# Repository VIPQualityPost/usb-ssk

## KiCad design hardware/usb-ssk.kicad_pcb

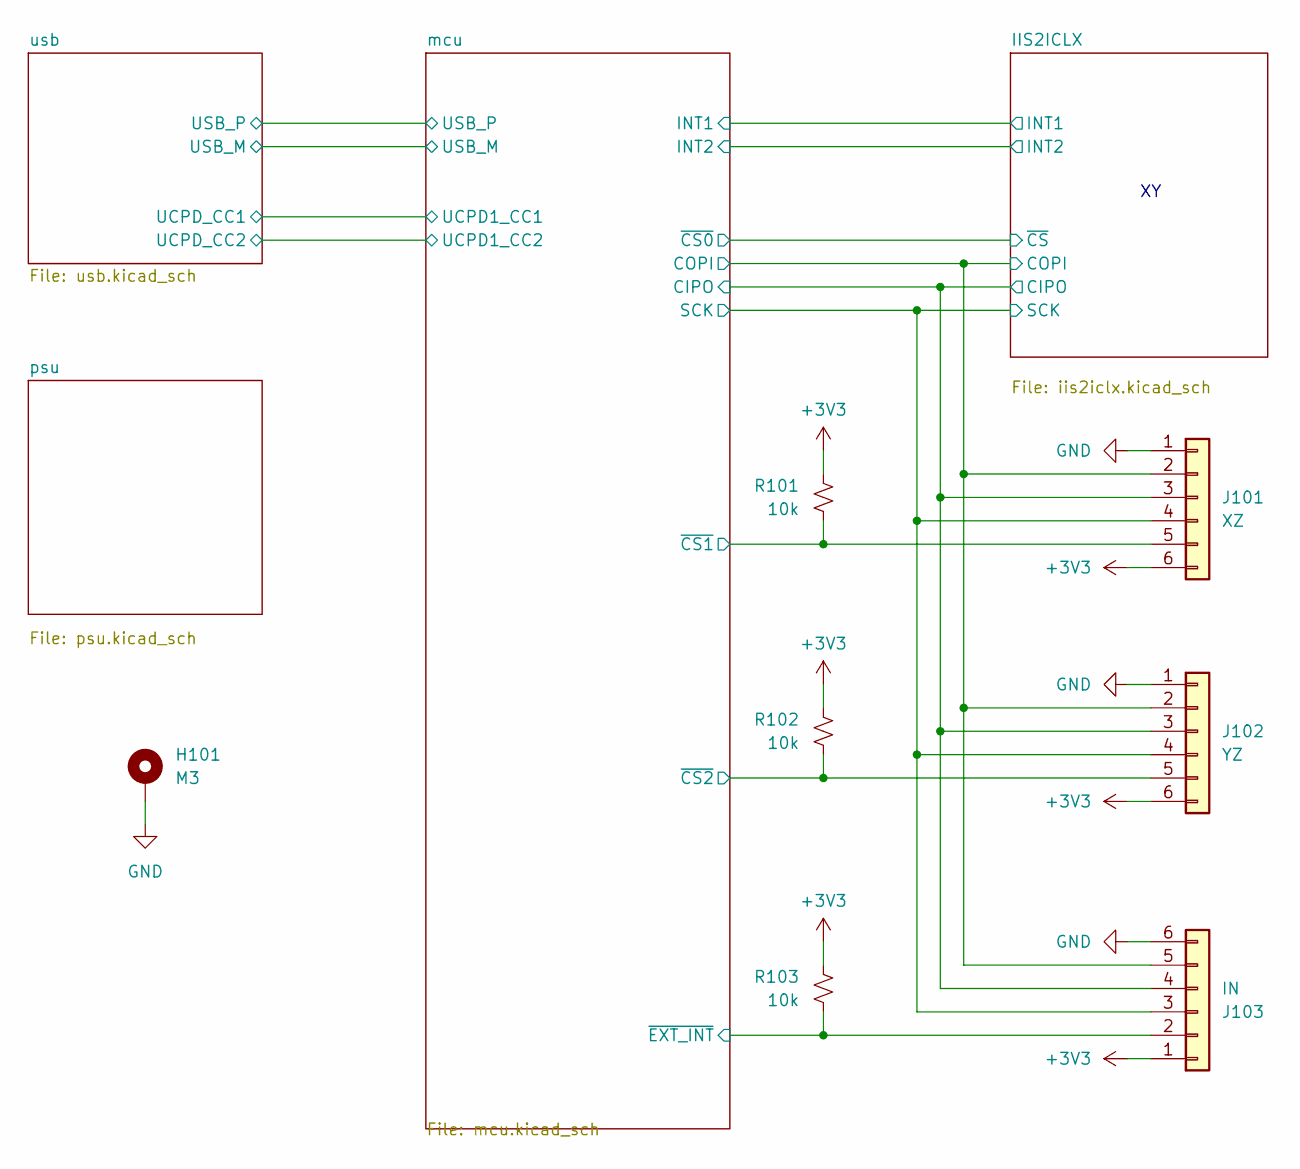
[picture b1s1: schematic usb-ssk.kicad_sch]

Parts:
H101: M3; MountingHole_3.2mm_M3_DIN965_Pad
J101: XZ; FPC-SMD_6P-P0.50_XUNPU_FPC-05F-6PH20; LCSC ID C2856796
J102: YZ; FPC-SMD_6P-P0.50_XUNPU_FPC-05F-6PH20; LCSC ID C2856796
J103: IN; FPC-SMD_6P-P0.50_XUNPU_FPC-05F-6PH20; LCSC ID C2856796
R101, R102, R103: 10k; R_0402_1005Metric; LCSC ID C25744

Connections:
+3V3: J101.6, J102.6, J103.1, R101.1, R102.1, R103.1; also elsewhere on the board
/IIS2ICLX/CIPO: J101.3, J102.3, J103.4; also elsewhere on the board
/IIS2ICLX/COPI: J101.2, J102.2, J103.5; also elsewhere on the board
/IIS2ICLX/SCK: J101.4, J102.4, J103.3; also elsewhere on the board
/mcu/~CS1: J101.5, R101.2; also elsewhere on the board
/mcu/~CS2: J102.5, R102.2; also elsewhere on the board
/mcu/~EXT_INT: J103.2, R103.2; also elsewhere on the board
GND: H101.1, J101.1, J102.1, J103.6; also elsewhere on the board

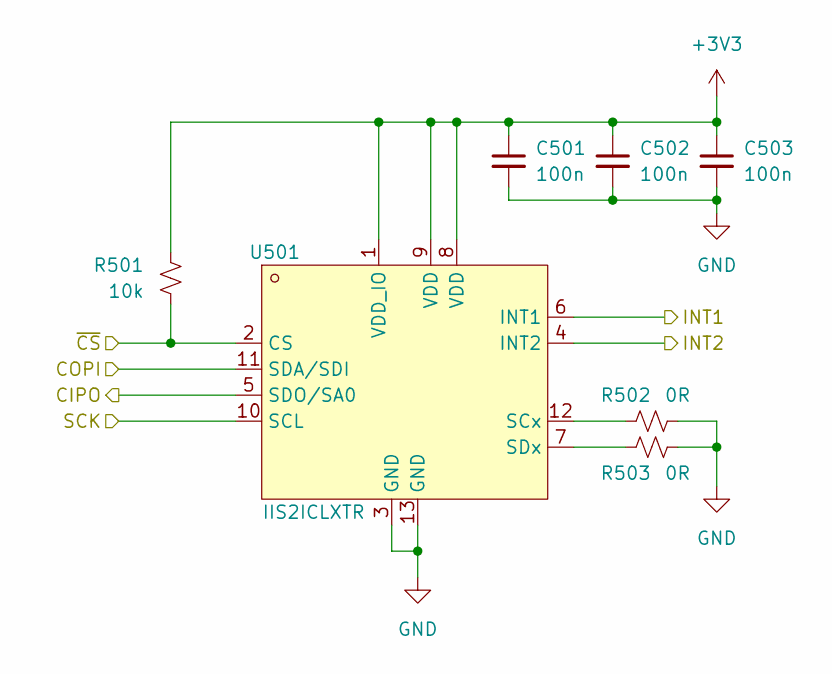
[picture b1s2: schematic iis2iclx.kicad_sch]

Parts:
C501, C502, C503: 100n; C_0402_1005Metric; LCSC ID C1525
R501: 10k; R_0402_1005Metric; LCSC ID C25744
R502, R503: 0R; R_0402_1005Metric; LCSC ID C17168
U501: IIS2ICLXTR; LGA16-L; LCSC ID C1857737

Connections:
+3V3: C501.1, C502.1, C503.1, R501.1, U501.1 (VDD_IO), U501.8 (VDD), U501.9 (VDD); also elsewhere on the board
/IIS2ICLX/CIPO: U501.5 (SDO/SA0); also elsewhere on the board
/IIS2ICLX/COPI: U501.11 (SDA/SDI); also elsewhere on the board
/IIS2ICLX/INT1: U501.6 (INT1); also elsewhere on the board
/IIS2ICLX/INT2: U501.4 (INT2); also elsewhere on the board
/IIS2ICLX/SCK: U501.10 (SCL); also elsewhere on the board
/IIS2ICLX/~CS: R501.2, U501.2 (CS); also elsewhere on the board
GND: C501.2, C502.2, C503.2, R502.2, R503.2, U501.3 (GND), U501.13 (GND); also elsewhere on the board
unnamed: R502.1, U501.12 (SCx)
unnamed: R503.1, U501.7 (SDx)

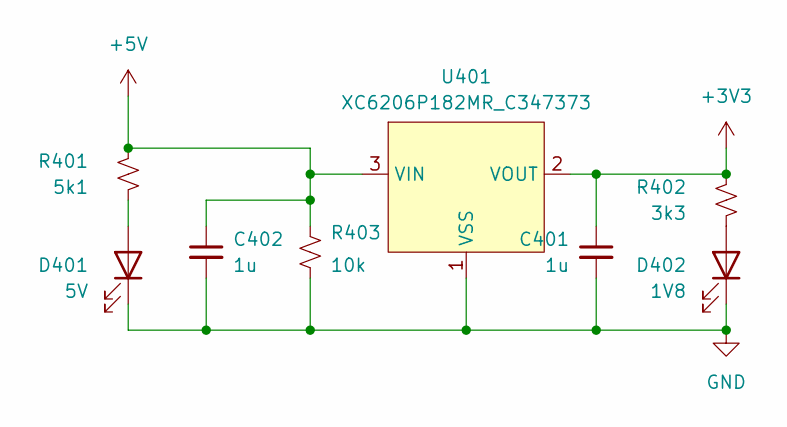
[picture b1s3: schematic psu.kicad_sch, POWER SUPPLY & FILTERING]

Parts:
C401, C402: 1u; C_0402_1005Metric; LCSC ID C52923
D401: 5V; D_0603_1608Metric; LCSC ID C2290
D402: 1V8; D_0603_1608Metric; LCSC ID C2290
R401: 5k1; R_0402_1005Metric; LCSC ID C25905
R402: 3k3; R_0402_1005Metric; LCSC ID C25890
R403: 10k; R_0402_1005Metric; LCSC ID C25744
U401: XC6206P182MR_C347373; SOT-23-3_L3.0-W1.7-P0.95-LS2.9-BR; LCSC Part C347373

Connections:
+3V3: C401.1, R402.1, U401.2 (VOUT); also elsewhere on the board
+5V: C402.1, R401.1, R403.1, U401.3 (VIN); also elsewhere on the board
GND: C401.2, C402.2, D401.1 (K), D402.1 (K), R403.2, U401.1 (VSS); also elsewhere on the board
unnamed: D401.2 (A), R401.2
unnamed: D402.2 (A), R402.2

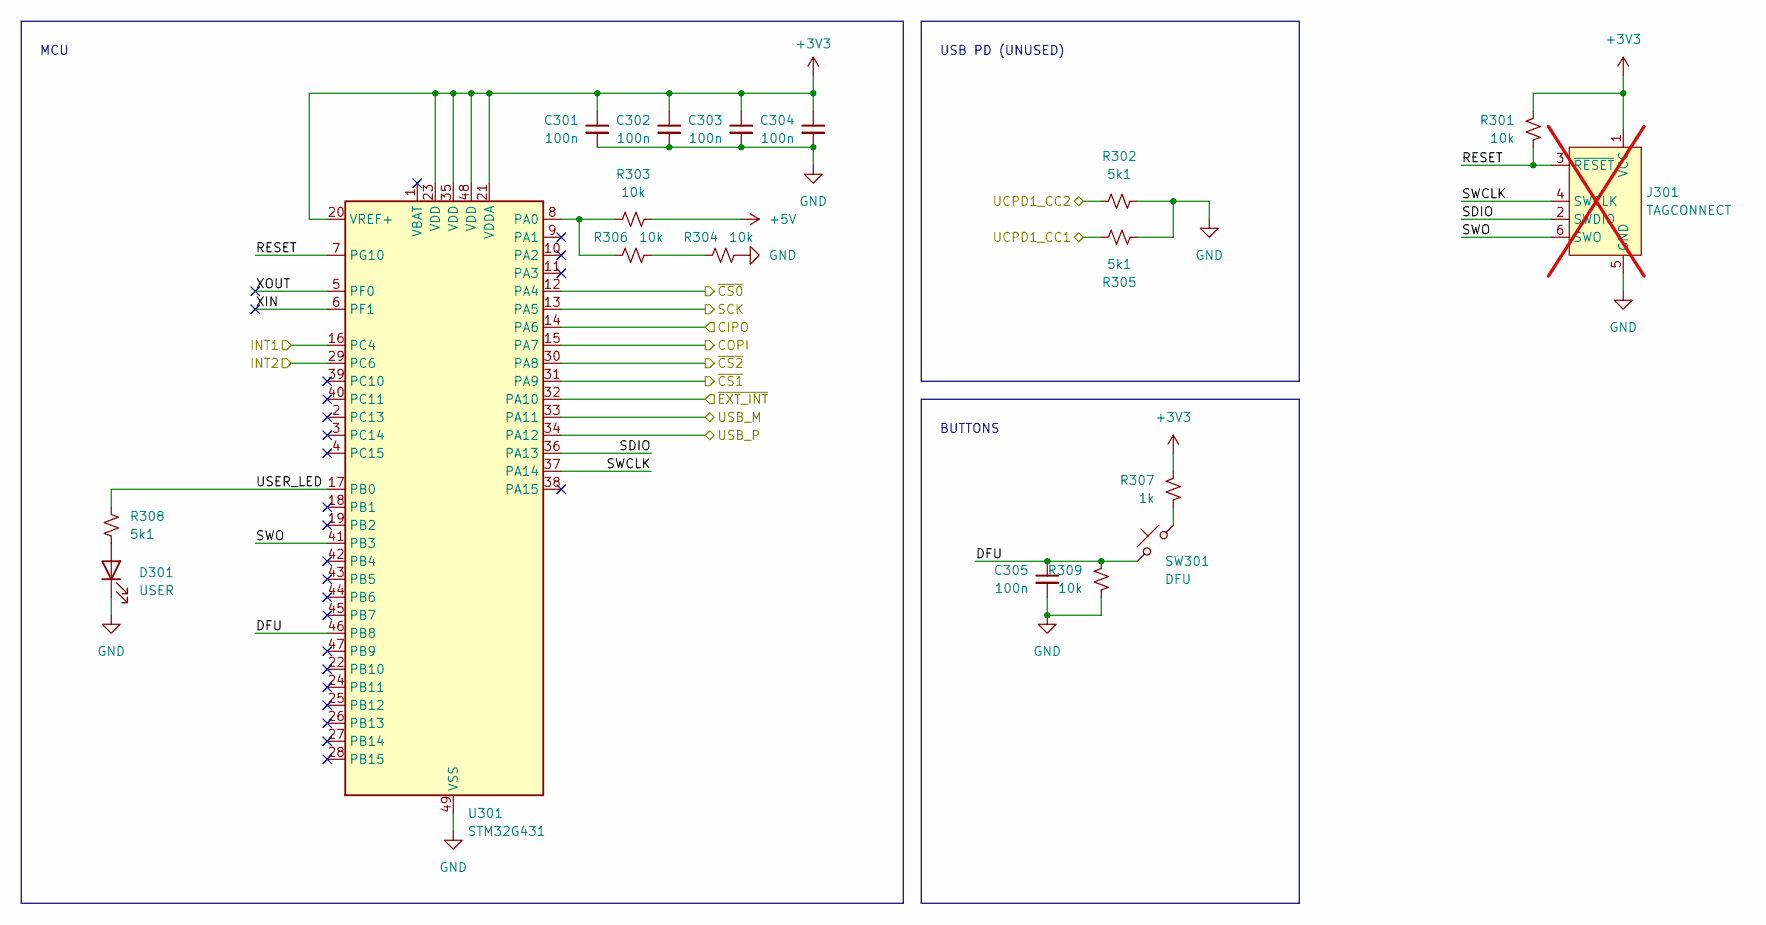
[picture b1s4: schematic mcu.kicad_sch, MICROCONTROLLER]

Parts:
C301, C302, C303, C304, C305: 100n; C_0402_1005Metric; LCSC ID C1525
D301: USER; D_0603_1608Metric; LCSC ID C2290
J301: TAGCONNECT; Tag-Connect_TC2030-IDC-NL_2x03_P1.27mm_Vertical; not fitted
R301, R303, R304, R306, R309: 10k; R_0402_1005Metric; LCSC ID C25744
R302, R305, R308: 5k1; R_0402_1005Metric; LCSC ID C25905
R307: 1k; R_0402_1005Metric; LCSC ID C11702
SW301: DFU; TS-1187A-B-A-B; LCSC ID C318884
U301: STM32G431; QFN-48-1EP_7x7mm_P0.5mm_EP5.6x5.6mm; LCSC ID C529356

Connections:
+3V3: C301.1, C302.1, C303.1, C304.1, J301.1 (VCC), R301.1, R307.1, U301.20 (VREF+), U301.21 (VDDA), U301.23 (VDD), U301.35 (VDD), U301.48 (VDD); also elsewhere on the board
+5V: R303.2; also elsewhere on the board
/IIS2ICLX/CIPO: U301.14 (PA6); also elsewhere on the board
/IIS2ICLX/COPI: U301.15 (PA7); also elsewhere on the board
/IIS2ICLX/INT1: U301.16 (PC4); also elsewhere on the board
/IIS2ICLX/INT2: U301.29 (PC6); also elsewhere on the board
/IIS2ICLX/SCK: U301.13 (PA5); also elsewhere on the board
/IIS2ICLX/~CS: U301.12 (PA4); also elsewhere on the board
/mcu/DFU: C305.1, R309.1, SW301.1, U301.46 (PB8)
/mcu/RESET: J301.3 (~RESET), R301.2, U301.7 (PG10)
/mcu/SDIO: J301.2 (SWDIO), U301.36 (PA13)
/mcu/SWCLK: J301.4 (SWCLK), U301.37 (PA14)
/mcu/SWO: J301.6 (SWO), U301.41 (PB3)
/mcu/UCPD1_CC1: R305.2; also elsewhere on the board
/mcu/UCPD1_CC2: R302.1; also elsewhere on the board
/mcu/USBD_M: U301.33 (PA11); also elsewhere on the board
/mcu/USBD_P: U301.34 (PA12); also elsewhere on the board
/mcu/USER_LED: R308.1, U301.17 (PB0)
/mcu/XIN: U301.6 (PF1)
/mcu/XOUT: U301.5 (PF0)
/mcu/~CS1: U301.31 (PA9); also elsewhere on the board
/mcu/~CS2: U301.30 (PA8); also elsewhere on the board
/mcu/~EXT_INT: U301.32 (PA10); also elsewhere on the board
GND: C301.2, C302.2, C303.2, C304.2, C305.2, D301.1 (K), J301.5 (GND), R302.2, R304.2, R305.1, R309.2, U301.49 (VSS); also elsewhere on the board
unnamed: D301.2 (A), R308.2
unnamed: R304.1, R306.2
unnamed: R307.2, SW301.2
unnamed: R303.1, R306.1, U301.8 (PA0)

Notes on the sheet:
BUTTONS
MCU
USB PD (UNUSED)

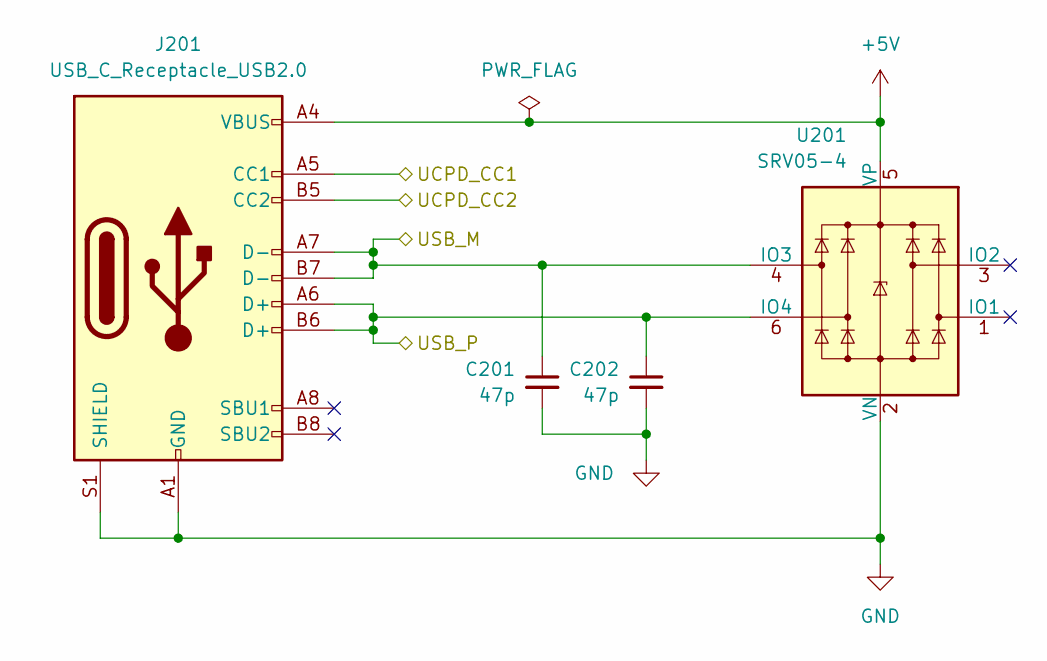
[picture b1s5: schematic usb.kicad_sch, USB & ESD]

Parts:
C201, C202: 47p; C_0402_1005Metric; LCSC ID C1567
J201: USB_C_Receptacle_USB2.0; USB_C_Receptacle_HRO_TYPE-C-31-M-12; LCSC ID C165948
U201: SRV05-4; SOT-23-6; LCSC ID C7420376

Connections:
+5V: J201.A4 (VBUS), J201.A9 (VBUS), J201.B4 (VBUS), J201.B9 (VBUS), U201.5 (VP); also elsewhere on the board
/mcu/UCPD1_CC1: J201.A5 (CC1); also elsewhere on the board
/mcu/UCPD1_CC2: J201.B5 (CC2); also elsewhere on the board
/mcu/USBD_M: C201.1, J201.A7 (D-), J201.B7 (D-), U201.4 (IO3); also elsewhere on the board
/mcu/USBD_P: C202.1, J201.A6 (D+), J201.B6 (D+), U201.6 (IO4); also elsewhere on the board
GND: C201.2, C202.2, J201.A1 (GND), J201.A12 (GND), J201.B1 (GND), J201.B12 (GND), J201.S1 (SHIELD), U201.2 (VN); also elsewhere on the board

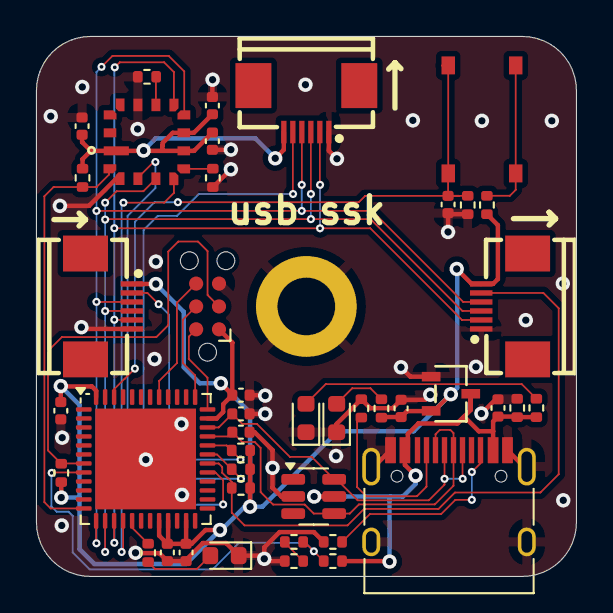
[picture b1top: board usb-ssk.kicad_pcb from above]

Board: 4 copper layers, 30.0 x 30.0 mm, 44 parts (0 on the bottom side), 30 nets.

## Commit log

2023-08-24 prototype firmware
2023-08-25 get float print support working
2023-08-25 start on schematic and software
2023-08-28 get graph and noise measurements working
2024-10-06 migrate to new IIS2ICLX accelerometer
2024-10-30 new hardware layout for IIS2ICLX
2024-10-30 add hardware documentation workflow
2024-10-30 Add design file PDFs to repo [skip ci]
2024-10-30 add dimensions to pcb
